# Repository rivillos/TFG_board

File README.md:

# TFG_board

design and fabrication files of PCB
bring-up files
C files examples

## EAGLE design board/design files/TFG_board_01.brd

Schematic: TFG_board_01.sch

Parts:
5V_BAT: TESTPAD/W_HOLE_1X1
AIN2, AIN3, AIN5, AIN6: HOLE
C1, C2, C14, C16, C17, C18, C19: 0.1uF, 6.3V; C0402
C3: 1nF, 50V; C0402
C4, C5, C6, C7: 18pF 50V; C0402
C8, C9, C10, C12: 0.1uF 6.3V; C0402
C11: 220uF 6.3V; B/3528-21R
C13, C15: 10uF, 10V; C0805
C20: 2.2uF; C0402
C21: 0.1uF; C0402
D1, D2, D3, D4, D5, D6: LTST-C191TBKT; EIA-STD
FB1: 0.1Ohm; C0805
FB2: 150Ohm, 800mA; C0805
GND, GND3, GND.: TESTPAD/W_HOLE_1X1
IC1: EMMC04G-S100-B08U; MICRON_EMMC_153
J1: 104031-0811; MOLEX_104031-0811
JTAG: CTI-JTAG
LPGD: TPTP15R; TP15R
MGT1, MGT2, MGT3, MGT4: MOUNTING_HOLE
NINT: TPTP15R; TP15R
NWKP: TPTP15R; TP15R
PGD: TPTP15R; TP15R
PWREN: TPTP15R; TP15R
Q1: MMBT2907SMD; SOT23-BEC
R1: 0.1R; R0805
R2: 0R; R0402
R3, R4: 1K5 1%; R0402
R5: 1K 1%; R0402
R6: 499R 1%; R0402
R7: 10K 1%; R0402
R8: 40.2K 1%; R0402
R9: 1K; R0402
R10, R17, R18, R19, R20, R21, R22, R23, R24, R25, R26, R27, R28, R29, R30, R31, R32: 100K; R0402
R11: 1M; R0402
R12: R-US_R0402; R0402
R13, R34, R35, R37, R38, R39, R40, R41, R42, R43, R44, R45, R46, R47, R48, R49, R50, R51, R52, R53, R54, R56: 10K; R0402
R14, R15, R16: 4K75; R0402
R33, R57, R58, R59, R60: 1K5; R0402
R36: 0 Ohm; R0805
R55: 33, 5%; R0402
S1, S2, S3, S4: KMR231GLFS; SW4SMD_63X161LS
SCL: HOLE
SDA: HOLE
SPI0_CS, SPI0_MISO, SPI0_MOSI, SPI0_SCK: HOLE
SYS_RTC_1P8V: TESTPAD/W_HOLE_1X1
SYS_VDD1_3P3V, SYS_VDD2_3P3V: TESTPAD/W_HOLE_1X1
SYS_VDD_1P8V: TESTPAD/W_HOLE_1X1
SYS_VOUT: TESTPAD/W_HOLE_1X1
T_BAT: TESTPAD/W_HOLE_1X1
U1: OSD3358-512M-BAS; OSD335X-BGA-400
U2: TLVH431; SOT23-3
U3: SN74LVC1G07_DCK_5; DCK5
U4: APX811SOT; SOT143-R
U5: TPS2051; S-PDSO-G08
U6, U7: TPD4S012_DRY_6; DRY6
U8: 24LC32A; SOT23-5
U$1, U$2, U$3, U$4, U$5, U$6, U$7, U$8, U$10, U$11, U$12, U$13: HOLE
UART0_RXD, UART0_TXD: HOLE
USB_DC: TESTPAD/W_HOLE_1X1
VDDSHV_3P3V: TESTPAD/W_HOLE_1X1
VDDS_DDR: TESTPAD/W_HOLE_1X1
VDDS_PLL: TESTPAD/W_HOLE_1X1
VDD_5V: TESTPAD/W_HOLE_1X1
VDD_ADC: TESTPAD/W_HOLE_1X1
VDD_CORE: TESTPAD/W_HOLE_1X1
VDD_MPU: TESTPAD/W_HOLE_1X1
V_BAT: TESTPAD/W_HOLE_1X1
WP: TESTPAD/W_HOLE_1X1
WRST: TPTP15R; TP15R
X1: PJ-102B_POWER_CON
X2: 10118192-0001LF; 10118192-0001LF(MICRO-USB-B-AMPHENOL-FCI)
X3: USB_HOST_W/CHASSIS_GND; USB_HOST_HORIZONTAL_W/CHASSIS_GND
Y1: 7A-24.000MAAJ-T; CRYSTAL-TXC-7A
Y2: ABS07-32.768KHZ-T; CRYSTAL_3.2X1.5

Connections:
AGND: C1.1, C2.1, C3.1, U1.A6 (VSSA_ADC), U1.A9 (VSSA_ADC), U1.E8 (VSSA_ADC)
CGND: MGT1.P$1, MGT2.P$1, MGT3.P$1, MGT4.P$1, R1.2, X2.CGND1 (SGND1), X2.CGND2 (SGND2), X2.CGND3 (SGND3), X2.CGND4 (SGND4), X2.CGND5 (SGND5), X2.CGND6 (SGND6), X3.5 (CG1), X3.6 (CG2)
CS: SPI0_CS.P$1, U1.A16 (SPI0_CS0)
EMMC_RSTN: IC1.K5 (RST#), R44.1, U1.R14 (GPMC_A04)
GND: C8.1, C9.1, C10.2, C11.-, C12.2, C13.2, C14.2, C15.2, C16.2, C17.2, C18.2, C19.2, C20.2, C21.2, D1.2 (C), GND.P$1, GND3.P$1, GND..P$1, IC1.C4 (VSSQ1), IC1.E7 (VSS1), IC1.G5 (VSS2), IC1.H10 (VSS3), IC1.K8 (VSS4), IC1.N2 (VSSQ2), IC1.N5 (VSSQ3), IC1.P4 (VSSQ4), IC1.P6 (VSSQ5), J1.6 (VSS), J1.10 (CARD_DET2), J1.G1 (GND), J1.G2 (GND), J1.G3 (GND), J1.G4 (GND), JTAG.4 (TDIS), JTAG.8 (GND1), JTAG.10 (GND2), JTAG.12 (GND3), JTAG.16 (GND4), JTAG.20 (GND5), R1.1, R10.1, R13.2, R15.1, R17.1, R18.1, R19.1, R22.1, R23.1, R24.1, R25.1, R26.1, R27.1, R28.1, R29.1, R30.1, R32.1, R33.1, R34.1, R57.1, R58.1, R59.1, R60.1, S1.1, S1.3, S2.2, S2.4, S3.2, S3.4, S4.2, S4.4, U1.A1 (VSS), U1.A18 (VSS), U1.E19 (VSS), U1.E20 (VSS), U1.F8 (VSS), U1.F19 (VSS), U1.G8 (VSS), U1.G9 (VSS), U1.G11 (VSS), U1.G12 (VSS), U1.G19 (VSS), U1.H6 (VSS), U1.H7 (VSS), U1.H8 (VSS), U1.H9 (VSS), U1.H10 (VSS), U1.H12 (VSS), U1.H19 (VSS), U1.J6 (VSS), U1.J7 (VSS), U1.J8 (VSS), U1.J9 (VSS), U1.J10 (VSS), U1.J11 (VSS), U1.J19 (VSS), U1.J20 (VSS), U1.K7 (VSS), U1.K9 (VSS), U1.K10 (VSS), U1.K11 (VSS), U1.K19 (VSS), U1.L10 (VSS), U1.L11 (VSS), U1.L12 (VSS), U1.L13 (VSS), U1.L19 (VSS), U1.M6 (VSS), U1.M7 (VSS), U1.M8 (VSS), U1.M9 (VSS), U1.M10 (VSS), U1.M12 (VSS), U1.M14 (VSS), U1.M19 (VSS), U1.N7 (VSS), U1.N10 (VSS), U1.N11 (VSS), U1.N14 (VSS), U1.N19 (VSS), U1.N20 (VSS), U1.P17 (USB1_ID), U1.P19 (VSS), U1.P20 (VSS), U1.R19 (VSS), U1.R20 (VSS), U1.T19 (VSS), U1.T20 (VSS), U1.U19 (VSS), U1.V1 (VSS), U1.V18 (VSS), U1.V19 (VSS), U1.W2 (VSS), U1.W3 (VSS), U1.W5 (VSS), U1.W6 (VSS), U1.W7 (VSS), U1.W8 (VSS), U1.W9 (VSS), U1.W10 (VSS), U1.W11 (VSS), U1.W12 (VSS), U1.W13 (VSS), U1.W14 (VSS), U1.W15 (VSS), U1.W16 (VSS), U1.W17 (VSS), U1.W18 (VSS), U1.W19 (VSS), U1.W20 (VSS), U1.Y7 (VSS), U1.Y10 (VSS), U1.Y12 (VSS), U1.Y15 (VSS), U1.Y18 (VSS), U3.3 (GND), U4.1 (GND), U5.1 (GND), U5.TH (PAD), U6.4 (GND), U7.4 (GND), U8.2 (VSS), X1.OUT, X2.GND, X3.4 (GND)
I2C0_SCL: R4.1, SDA.P$1, U1.C16 (I2C0_SCL), U1.C20 (PMIC_IN_I2C_SCL), U8.1 (SCL)
I2C0_SDA: R3.1, SCL.P$1, U1.C17 (I2C0_SDA), U1.C19 (PMIC_IN_I2C_SDA), U8.3 (SDA)
JTAG_EMU0: JTAG.13 (EMU0), R14.1, U1.C14 (EMU0)
JTAG_EMU1: JTAG.14 (EMU1), R16.1, U1.B14 (EMU1)
JTAG_EMU2: JTAG.17 (EMU2), U1.A15 (XDMA_EVENT_INTR0)
JTAG_EMU3: JTAG.18 (EMU3), U1.D14 (XDMA_EVENT_INTR1)
JTAG_TCK: JTAG.9 (TCKRTN), JTAG.11 (TCK), U1.A12 (TCK)
JTAG_TDI: JTAG.3 (TDI), U1.B11 (TDI)
JTAG_TDO: JTAG.7 (TDO), U1.A11 (TDO)
JTAG_TMS: JTAG.1 (TMS), U1.C11 (TMS)
JTAG_TRSTN: JTAG.2 (TRSTN), R15.2, U1.B10 (TRSTN)
LCD_DATA0: R17.2, U1.R1 (LCD_DATA00)
LCD_DATA1: R18.2, U1.R2 (LCD_DATA01)
LCD_DATA2: R19.2, U1.R3 (LCD_DATA02)
LCD_DATA3: R20.1, U1.R4 (LCD_DATA03)
LCD_DATA4: R21.1, U1.T1 (LCD_DATA04)
LCD_DATA5: R22.2, U1.T2 (LCD_DATA05)
LCD_DATA6: R23.2, U1.T3 (LCD_DATA06)
LCD_DATA7: R24.2, U1.T4 (LCD_DATA07)
LCD_DATA8: R25.2, U1.U1 (LCD_DATA08)
LCD_DATA9: R26.2, U1.U2 (LCD_DATA09)
LCD_DATA10: R27.2, U1.U3 (LCD_DATA10)
LCD_DATA11: R28.2, U1.U4 (LCD_DATA11)
LCD_DATA12: R29.2, U1.V2 (LCD_DATA12), U$2.P$1
LCD_DATA13: R30.2, U1.V3 (LCD_DATA13), U$3.P$1
LCD_DATA14: R31.1, U1.V4 (LCD_DATA14)
LCD_DATA15: R32.2, U1.T5 (LCD_DATA15)
MISO: SPI0_MISO.P$1, U1.B17 (SPI0_D0)
MMC0_CD: J1.9 (CARD_DET1), JTAG.19 (EMU4), R43.1
MMC0_CLKO: J1.5 (CLK), R40.1, U1.G17 (MMC0_CLK)
MMC0_CMD: J1.3 (CMD), R39.1, U1.C15 (SPI0_CS1), U1.G18 (MMC0_CMD)
MMC0_DAT0: J1.7 (DAT0), R37.1, U1.G16 (MMC0_DAT0)
MMC0_DAT1: J1.8 (DAT1), R38.1, U1.G15 (MMC0_DAT1)
MMC0_DAT2: J1.1 (DAT2), R41.1, U1.F18 (MMC0_DAT2)
MMC0_DAT3: J1.2 (CD/DAT3), R42.1, U1.F17 (MMC0_DAT3)
MMC1_CLK: IC1.M6 (CLK), R45.1, R55.2
MMC1_CMD: IC1.M5 (CMD), R46.1, U1.V9 (GPMC_CSN2)
MMC1_DAT0: IC1.A3 (DAT0), R54.1, U1.U7 (GPMC_AD00)
MMC1_DAT1: IC1.A4 (DAT1), R53.1, U1.V7 (GPMC_AD01)
MMC1_DAT2: IC1.A5 (DAT2), R52.1, U1.R8 (GPMC_AD02)
MMC1_DAT3: IC1.B2 (DAT3), R51.1, U1.T8 (GPMC_AD03)
MMC1_DAT4: IC1.B3 (DAT4), R50.1, U1.U8 (GPMC_AD04)
MMC1_DAT5: IC1.B4 (DAT5), R49.1, U1.V8 (GPMC_AD05)
MMC1_DAT6: IC1.B5 (DAT6), R48.1, U1.R9 (GPMC_AD06)
MMC1_DAT7: IC1.B6 (DAT7), R47.1, U1.T9 (GPMC_AD07)
MOSI: SPI0_MOSI.P$1, U1.B16 (SPI0_D1)
unnamed: SYS_RTC_1P8V.P$1, U1.D7 (SYS_RTC_1P8V)
unnamed: U1.E10 (VDDSHV_3P3V), VDDSHV_3P3V.P$1
unnamed: U1.T12 (GPMC_AD12), U$4.P$1
unnamed: 5V_BAT.P$1, U1.Y2 (VIN_BAT), U1.Y3 (VIN_BAT)
unnamed: U1.Y1 (BAT_VOLT), V_BAT.P$1
unnamed: T_BAT.P$1, U1.W1 (BAT_TEMP)
unnamed: SYS_VDD_1P8V.P$1, U1.E9 (SYS_VDD_1P8V)
unnamed: U1.F10 (VDD_MPU), VDD_MPU.P$1
unnamed: U1.F6 (VDD_CORE), VDD_CORE.P$1
unnamed: U1.E5 (VDDS_DDR), VDDS_DDR.P$1
unnamed: U1.E7 (VDDS_PLL), VDDS_PLL.P$1
unnamed: U1.R12 (GPMC_AD13), U$5.P$1
unnamed: PWREN.TP, U1.C6 (PMIC_POWER_EN), U1.D19 (PMIC_IN_PWR_EN)
unnamed: C1.2, C2.2, C3.2, R2.2, U1.B9 (VREFP)
unnamed: LPGD.TP, U1.B5 (RTC_PWRONRSTN), U1.B20 (PMIC_OUT_LDO_PGOOD)
unnamed: NWKP.TP, U1.A19 (PMIC_OUT_NWAKEUP), U1.C5 (EXT_WAKEUP)
unnamed: NINT.TP, U1.B18 (EXTINTN), U1.B19 (PMIC_OUT_NINT)
unnamed: S1.2, S1.4, U1.D20 (PMIC_IN_PB_IN)
unnamed: D1.1 (A), R5.1
unnamed: R7.1, R8.2, U2.1 (REF)
unnamed: PGD.TP, U1.A20 (PMIC_OUT_PGOOD), U1.B15 (PWRONRSTN), U3.2 (A)
unnamed: Q1.B, R6.1, U2.2 (CATHODE)
unnamed: S2.1, S2.3, U3.4 (Y), U4.3 (MR#)
unnamed: R9.1, U4.2 (RESET#)
unnamed: D2.1 (A), U1.U14 (GPMC_A02)
unnamed: C4.2, R11.2, U1.M20 (OSC0_IN), Y1.P$1 (1)
unnamed: C5.2, R11.1, U1.K20 (OSC0_OUT), Y1.P$2 (2)
unnamed: C6.2, R12.2, U1.H20 (OSC1_IN), Y2.P$2
unnamed: C7.2, R12.1, U1.F20 (OSC1_OUT), Y2.P$1
unnamed: C4.1, C5.1, U1.L20 (OSC0_GND)
unnamed: C6.1, C7.1, U1.G20 (OSC1_GND)
unnamed: R13.1, U1.B4 (RTC_KALDO_ENN)
unnamed: D2.2 (C), R33.2
unnamed: S3.1, S3.3, U1.U16 (GPMC_A09)
unnamed: U1.R13 (GPMC_A00), U$1.P$1
unnamed: FB2.2, X3.1 (VBUS)
unnamed: U1.T14 (GPMC_A03), U$6.P$1
unnamed: U1.B12 (MCASP0_ACLKR), U$8.P$1
unnamed: S4.1, S4.3, U1.V17 (GPMC_A11)
unnamed: R55.1, U1.U9 (GPMC_CSN1)
unnamed: U1.C13 (MCASP0_FSR), U$7.P$1
unnamed: R56.1, U8.5 (WP), WP.P$1
unnamed: AIN2.P$1, U1.B7 (AIN2)
unnamed: AIN3.P$1, U1.A7 (AIN3)
unnamed: AIN5.P$1, U1.B8 (AIN5)
unnamed: AIN6.P$1, U1.A8 (AIN6)
unnamed: R36.2, X2.VBUS
unnamed: U1.A13 (MCASP0_ACLKX), U$10.P$1
unnamed: U1.A14 (MCASP0_AHCLKX), U$11.P$1
unnamed: D3.2 (C), R57.2
unnamed: D4.2 (C), R58.2
unnamed: D5.2 (C), R59.2
unnamed: D6.2 (C), R60.2
unnamed: C20.1, IC1.C2 (VDDI)
PWM_2A: U1.U10 (GPMC_AD08), U$12.P$1
PWM_2B: U1.T10 (GPMC_AD09), U$13.P$1
SCK: SPI0_SCK.P$1, U1.A17 (SPI0_SCLK)
SYS_ADC_1P8V: R2.1, U1.A4 (SYS_ADC_1P8V), U1.A5 (SYS_ADC_1P8V), U1.D8 (SYS_ADC_1P8V), VDD_ADC.P$1
SYS_RSTN: C9.2, JTAG.15 (SRST), R9.2, R10.2, U1.A10 (WARMRSTN), WRST.TP
SYS_RTC_1P8V: Q1.C, R8.1, U1.P9 (SYS_RTC_1P8V), U1.P14 (SYS_RTC_1P8V), U2.3 (ANODE), U3.5 (VCC)
SYS_VDD1_3P3V: C8.2, C13.1, C14.1, C15.1, C16.1, C17.1, C18.1, C19.1, C21.1, IC1.C6 (VCCQ1), IC1.E6 (VCC1), IC1.F5 (VCC2), IC1.J10 (VCC3), IC1.K9 (VCC4), IC1.M4 (VCCQ2), IC1.N4 (VCCQ3), IC1.P3 (VCCQ4), IC1.P5 (VCCQ5), J1.4 (VDD), JTAG.5 (TVDD), R3.2, R4.2, R14.2, R16.2, R20.2, R21.2, R31.2, R35.2, R37.2, R38.2, R39.2, R40.2, R41.2, R42.2, R43.2, R44.2, R45.2, R46.2, R47.2, R48.2, R49.2, R50.2, R51.2, R52.2, R53.2, R54.2, R56.2, SYS_VDD1_3P3V.P$1, U1.U20 (SYS_VDD1_3P3V), U1.V20 (SYS_VDD1_3P3V), U4.4 (VCC), U8.4 (VCC)
SYS_VDD2_3P3V: R5.2, SYS_VDD2_3P3V.P$1, U1.Y11 (SYS_VDD2_3P3V)
SYS_VDD_1P8V: U1.R16 (SYS_VDD_1P8V)
SYS_VOUT: C11.+, SYS_VOUT.P$1, U1.W4 (SYS_VOUT), U1.Y4 (SYS_VOUT), U5.2 (IN1), U5.3 (IN2)
UART0_RX: U1.E15 (UART0_RXD), UART0_RXD.P$1
UART0_TX: U1.E16 (UART0_TXD), UART0_TXD.P$1
USB0_DM: U1.N18 (USB0_DM), U7.1 (D-), X2.D-
USB0_DP: U1.N17 (USB0_DP), U7.2 (D+), X2.D+
USB0_ID: U1.P16 (USB0_ID), U7.3 (ID), X2.ID
USB1_DM: U1.R18 (USB1_DM), U6.1 (D-), X3.2 (D-)
USB1_DP: U1.R17 (USB1_DP), U6.2 (D+), X3.3 (D+)
USB1_DRVVBUS: R34.2, U1.F15 (USB1_DRVVBUS), U5.4 (EN)
USB1_OCN: R35.1, U1.T16 (GPMC_A10), U5.5 (!OC)
USB1_PWR: C10.1, FB1.2, FB2.1, U5.6 (OUT1), U5.7 (OUT2), U5.8 (OUT3), U6.6 (VBUS)
USB1_VBUS: FB1.1, U1.T18 (USB1_VBUS)
USB_DC: C12.1, R36.1, U1.P15 (USB0_VBUS), U1.Y8 (VIN_USB), U1.Y9 (VIN_USB), U7.6 (VBUS), USB_DC.P$1
USR0: D3.1 (A), U1.V15 (GPMC_A05)
USR1: D4.1 (A), U1.U15 (GPMC_A06)
USR2: D5.1 (A), U1.T15 (GPMC_A07)
USR3: D6.1 (A), U1.V16 (GPMC_A08)
VDD_3V3A: Q1.E, R6.2, R7.2, U1.R15 (VDDSHV_3P3V)
VDD_5V: U1.Y5 (VIN_AC), U1.Y6 (VIN_AC), VDD_5V.P$1, X1.IN

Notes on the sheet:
Coger el más conveniente para el ruteado
Circuitería de Reset
Boot configuration: 0x4018
Va a un GPIO
Falta conectar todas las señales del USB al SiP
USB host
uSD CARD
JTAG
eMMC
EEPROM
User Leds
GPIO3_21
GPIO3_14
eQEP0A
eQEP0B
eQEP2A
eQEP2B
GPIO0_8
GPIO0_9
GPA3
GPA0
PWM_2A
PWM_2B

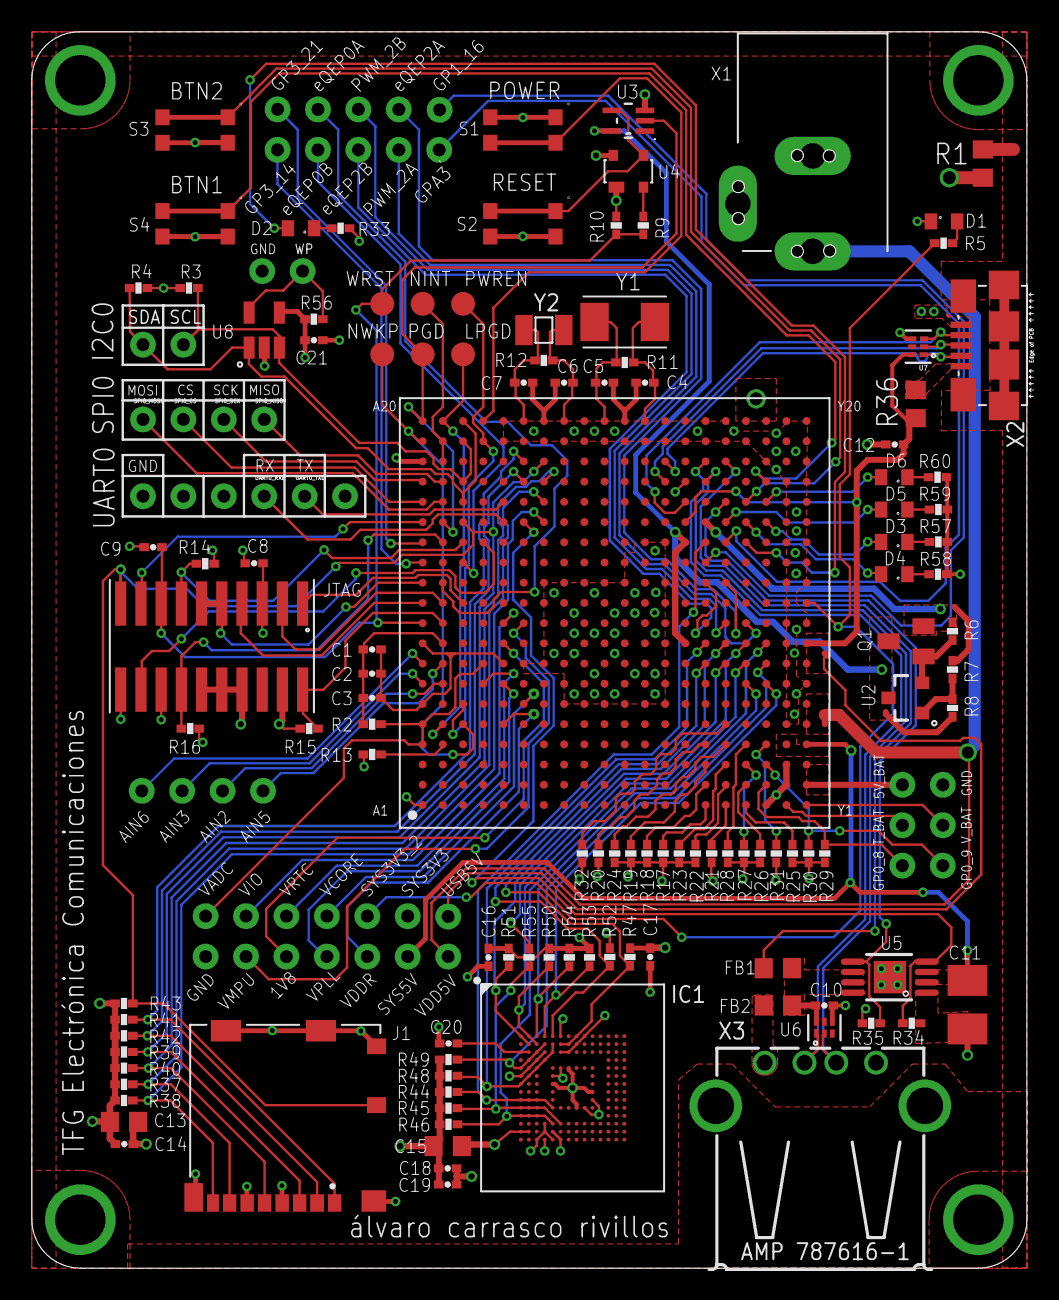
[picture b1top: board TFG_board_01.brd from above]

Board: 4 copper layers, 62.5 x 77.7 mm, 164 parts (0 on the bottom side), 132 nets.

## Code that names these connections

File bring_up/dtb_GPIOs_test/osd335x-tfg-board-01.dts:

//#SPDX-License-Identifier: GPL-2.0
/* Copyright (C) 2018 Octavo Systems LLC - http://www.octavosystems.com/
 *
 * This program is free software; you can redistribute it and/or modify
 * it under the terms of the GNU General Public License version 2 as
 * published by the Free Software Foundation.
 */

 /dts-v1/;

 #include "osd335x-sm.dtsi"

/ {

  model = "Octavo OSD335x-SM Reference Design";
  compatible = "oct,osd335x-reference-design", "ti,am335x-bone", "ti,am33xx";


	leds {
		pinctrl-names = "default", "sleep";
		pinctrl-0 = <&user_leds_default>;
		pinctrl-1 = <&user_leds_sleep>;

		compatible = "gpio-leds";

		led@2 {
			label = "beaglebone:green:usr0";
			gpios = <&gpio1 21 GPIO_ACTIVE_HIGH>;
			linux,default-trigger = "heartbeat";
			default-state = "off";
		};

		led@3 {
			label = "beaglebone:green:usr1";
			gpios = <&gpio1 22 GPIO_ACTIVE_HIGH>;
			linux,default-trigger = "mmc0";
			default-state = "off";
		};

		led@4 {
			label = "beaglebone:green:usr2";
			gpios = <&gpio1 23 GPIO_ACTIVE_HIGH>;
			linux,default-trigger = "cpu0";
			default-state = "off";
		};

		led@5 {
			label = "beaglebone:green:usr3";
			gpios = <&gpio1 24 GPIO_ACTIVE_HIGH>;
			linux,default-trigger = "mmc1";
			default-state = "off";
		};
	};

	vmmcsd_fixed: fixedregulator@0 {
		compatible = "regulator-fixed";
		regulator-name = "vmmcsd_fixed";
		regulator-min-microvolt = <3300000>;
		regulator-max-microvolt = <3300000>;
	};
};

&am33xx_pinmux {
	user_leds_default: user_leds_default {
		pinctrl-single,pins = <
			AM33XX_IOPAD(0x854, PIN_OUTPUT_PULLDOWN | MUX_MODE7)	 /* gpmc_a5.gpio1_21 */
			AM33XX_IOPAD(0x858, PIN_OUTPUT_PULLUP | MUX_MODE7)	 /* gpmc_a6.gpio1_22 */
			AM33XX_IOPAD(0x85c, PIN_OUTPUT_PULLDOWN | MUX_MODE7)	 /* gpmc_a7.gpio1_23 */
			AM33XX_IOPAD(0x860, PIN_OUTPUT_PULLUP | MUX_MODE7)	 /* gpmc_a8.gpio1_24 */
			//Los siguientes pines son para la configuración de los GPIOs de la TFG Board
			AM33XX_IOPAD(0x09AC, PIN_OUTPUT_PULLDOWN | MUX_MODE7 )  /*mcasp0_ahclkx gpio2[21]*/
        		AM33XX_IOPAD(0x0990, PIN_OUTPUT_PULLDOWN | MUX_MODE7 )  /*mcasp0_aclkx gpio3[14]*/
        		AM33XX_IOPAD(0x09A0, PIN_OUTPUT_PULLDOWN | MUX_MODE7 )  /*mcasp0_aclkr gpio3[18]*/
        		AM33XX_IOPAD(0x09A4, PIN_OUTPUT_PULLDOWN | MUX_MODE7 )  /*mcasp0_fsr gpio3[19]*/
			AM33XX_IOPAD(0x0824, PIN_OUTPUT_PULLDOWN | MUX_MODE7 )  /*gpmc_ad9 gpio0[23]*/
  			AM33XX_IOPAD(0x0834, PIN_OUTPUT_PULLDOWN | MUX_MODE7 )  /*gpmc_ad13 gpio1[13]*/
  			AM33XX_IOPAD(0x0830, PIN_OUTPUT_PULLDOWN | MUX_MODE7 )  /*gpmc_ad12 gpio1[12]*/
  			AM33XX_IOPAD(0x0820, PIN_OUTPUT_PULLDOWN | MUX_MODE7 )  /*gpmc_ad8  gpio1[12]*/
        		AM33XX_IOPAD(0x0840, PIN_OUTPUT_PULLDOWN | MUX_MODE7 )  /*gpmc_a0 gpio1[16]*/
  			AM33XX_IOPAD(0x084C, PIN_OUTPUT_PULLDOWN | MUX_MODE7 )  /*gpmc_a3 gpio1[19]*/
  			AM33XX_IOPAD(0x0848, PIN_OUTPUT_PULLDOWN | MUX_MODE7 )  /*gpmc_a0 (user led) gpio1[18]*/
  			AM33XX_IOPAD(0x0864, PIN_INPUT_PULLUP | MUX_MODE7 )     /*gpmc_a9 (button 1) gpio1[25]*/
  			AM33XX_IOPAD(0x086C, PIN_INPUT_PULLUP | MUX_MODE7 )     /*gpmc_a11 (button 2) gpio1[27]*/
		>;
	};

	user_leds_sleep: user_leds_sleep {
		pinctrl-single,pins = <
			AM33XX_IOPAD(0x854, PIN_INPUT_PULLDOWN | MUX_MODE7)	/* gpmc_a5.gpio1_21 */
			AM33XX_IOPAD(0x858, PIN_INPUT_PULLDOWN | MUX_MODE7)	/* gpmc_a6.gpio1_22 */
			AM33XX_IOPAD(0x85c, PIN_INPUT_PULLDOWN | MUX_MODE7)	/* gpmc_a7.gpio1_23 */
			AM33XX_IOPAD(0x860, PIN_INPUT_PULLDOWN | MUX_MODE7)	/* gpmc_a8.gpio1_24 */
		>;
	};
	
	i2c0_pins: pinmux_i2c0_pins {
		pinctrl-single,pins = <
			AM33XX_IOPAD(0x988, PIN_INPUT_PULLUP | MUX_MODE0)	/* i2c0_sda.i2c0_sda */
			AM33XX_IOPAD(0x98c, PIN_INPUT_PULLUP | MUX_MODE0)	/* i2c0_scl.i2c0_scl */
		>;
	};

	uart0_pins: pinmux_uart0_pins {
		pinctrl-single,pins = <
			AM33XX_IOPAD(0x970, PIN_INPUT_PULLUP | MUX_MODE0)	/* uart0_rxd.uart0_rxd */
			AM33XX_IOPAD(0x974, PIN_OUTPUT_PULLDOWN | MUX_MODE0)	/* uart0_txd.uart0_txd */
		>;
	};


	mmc1_pins: pinmux_mmc1_pins {
		pinctrl-single,pins = <
			AM33XX_IOPAD(0x960, PIN_INPUT | MUX_MODE7) /* GPIO0_6 */
		>;
	};

	emmc_pins: pinmux_emmc_pins {
		pinctrl-single,pins = <
			AM33XX_IOPAD(0x880, PIN_INPUT_PULLUP | MUX_MODE2) /* gpmc_csn1.mmc1_clk */
			AM33XX_IOPAD(0x884, PIN_INPUT_PULLUP | MUX_MODE2) /* gpmc_csn2.mmc1_cmd */
			AM33XX_IOPAD(0x800, PIN_INPUT_PULLUP | MUX_MODE1) /* gpmc_ad0.mmc1_dat0 */
			AM33XX_IOPAD(0x804, PIN_INPUT_PULLUP | MUX_MODE1) /* gpmc_ad1.mmc1_dat1 */
			AM33XX_IOPAD(0x808, PIN_INPUT_PULLUP | MUX_MODE1) /* gpmc_ad2.mmc1_dat2 */
			AM33XX_IOPAD(0x80c, PIN_INPUT_PULLUP | MUX_MODE1) /* gpmc_ad3.mmc1_dat3 */
			AM33XX_IOPAD(0x810, PIN_INPUT_PULLUP | MUX_MODE1) /* gpmc_ad4.mmc1_dat4 */
			AM33XX_IOPAD(0x814, PIN_INPUT_PULLUP | MUX_MODE1) /* gpmc_ad5.mmc1_dat5 */
			AM33XX_IOPAD(0x818, PIN_INPUT_PULLUP | MUX_MODE1) /* gpmc_ad6.mmc1_dat6 */
			AM33XX_IOPAD(0x81c, PIN_INPUT_PULLUP | MUX_MODE1) /* gpmc_ad7.mmc1_dat7 */
		>;
	};
};

&uart0 {
	pinctrl-names = "default";
	pinctrl-0 = <&uart0_pins>;

	status = "okay";
};

&usb {
	status = "okay";
};

&usb_ctrl_mod {
	status = "okay";
};

&usb0_phy {
	status = "okay";
};

&usb1_phy {
	status = "okay";
};

&usb0 {
	status = "okay";
	dr_mode = "peripheral";
};

&usb1 {
	status = "okay";
	dr_mode = "host";
};

&cppi41dma  {
	status = "okay";
};

&i2c0 {
	baseboard_eeprom: baseboard_eeprom@50 {
		compatible = "at,24c256";
		reg = <0x50>;

		#address-cells = <1>;
		#size-cells = <1>;
		baseboard_data: baseboard_data@0 {
			reg = <0 0x100>;
		};
	};
};

&tscadc {
	status = "okay";
};

&am335x_adc {
	ti,adc-channels = <0 1 2 3 4 5 6 7>;
};

&mmc1 {
	status = "okay";
	bus-width = <0x4>;
	pinctrl-names = "default";
	pinctrl-0 = <&mmc1_pins>;
	cd-gpios = <&gpio0 6 GPIO_ACTIVE_LOW>;
  vmmc-supply = <&vmmcsd_fixed>;
};

&aes {
	status = "okay";
};

&sham {
	status = "okay";
};

&wkup_m3_ipc {
	ti,scale-data-fw = "am335x-bone-scale-data.bin";
};

&rtc {
	clocks = <&clk_32768_ck>, <&clkdiv32k_ick>;
	clock-names = "ext-clk", "int-clk";
	system-power-controller;
};

&sgx {
	status = "okay";
};


&cpu0_opp_table {
	/*
	 * All PG 2.0 silicon may not support 1GHz but some of the early
	 * BeagleBone Blacks have PG 2.0 silicon which is guaranteed
	 * to support 1GHz OPP so enable it for PG 2.0 on this board.
	 */
	oppnitro@1000000000 {
		opp-supported-hw = <0x06 0x0100>;
	};
};

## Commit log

2020-07-13 Añadidos los archivos para la puesta en marcha de la placa
2021-09-20 repositorio completo del proyecto
2021-09-26 añadido sistema de archivos con busybox
2021-09-26 agregado imagen de buildroot
